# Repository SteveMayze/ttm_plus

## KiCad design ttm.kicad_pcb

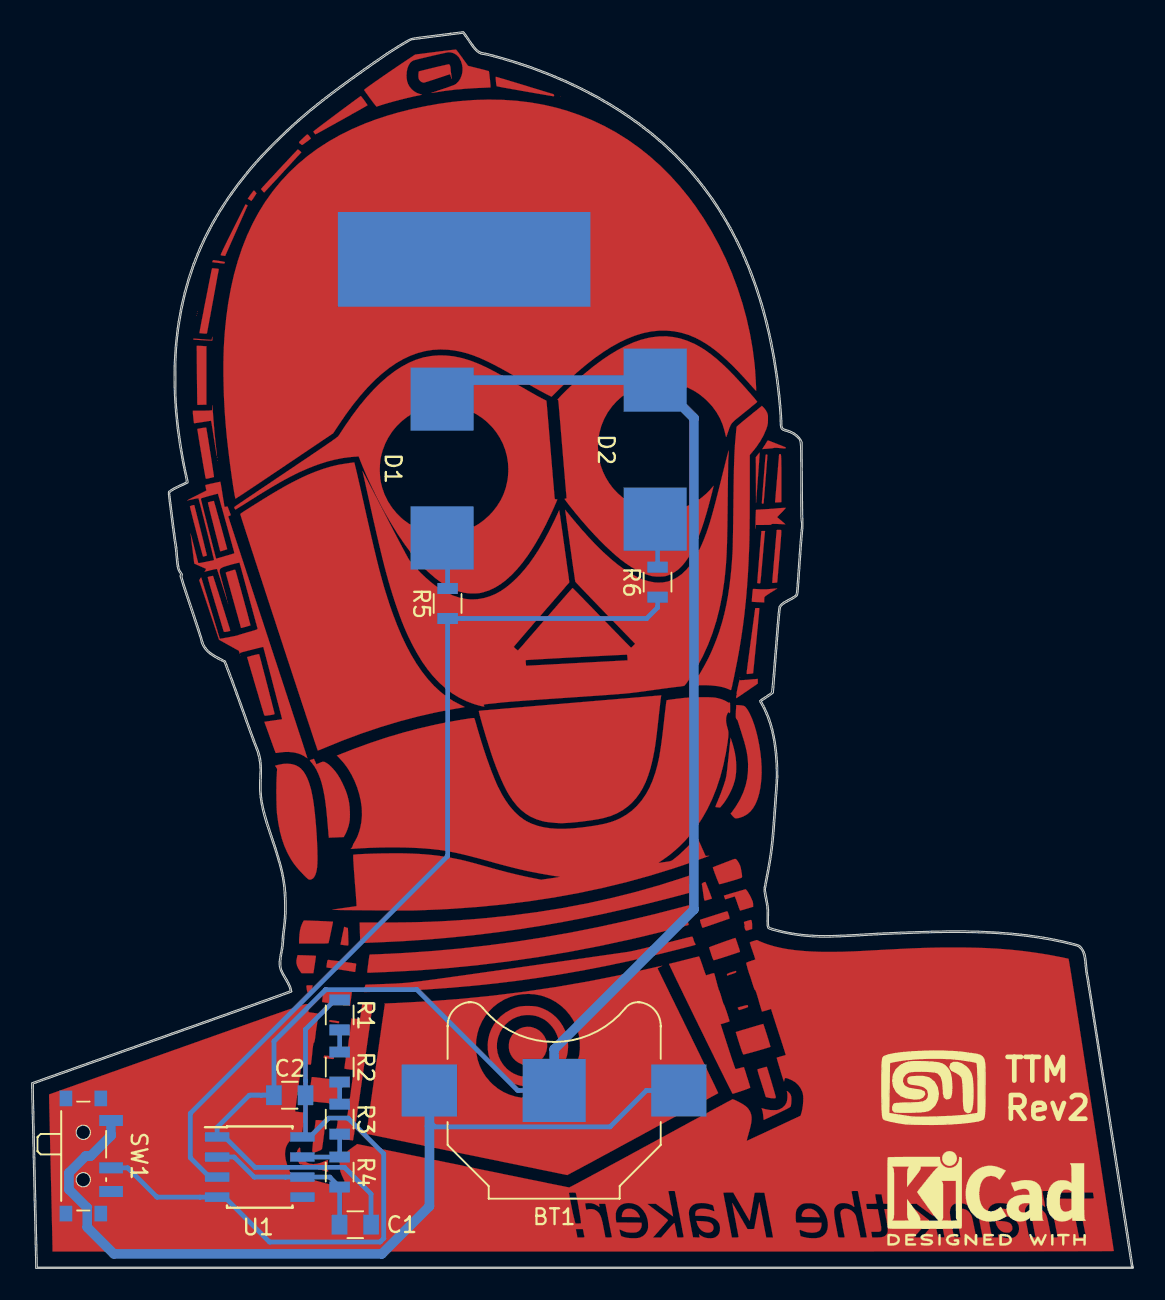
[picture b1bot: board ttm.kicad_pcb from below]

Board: 2 copper layers, 69.8 x 78.3 mm, 17 parts (15 on the bottom side), 10 nets.

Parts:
BT1: 3V; BatteryHolder_Keystone_3000_1x12mm
C1: 1μF; C_0805
C2: 0.1μF; C_0805
D1, D2: LED; LY_T77K_NH
Edge Cut: LOGO; c3po_EdgeCut
Front CU Text: LOGO; c3po_FCu_Text
KiCAD_Logo: KiCad-Logo2_6mm_SilkScreen
R1, R2, R3: 10MΩ; R_0805
R4: 750kΩ; R_0805
R5, R6: 400Ω; R_0805
SM_Logo: LOGO; MyBasic_rounded_50_1
SW1: SW_SPDT; SW_SPDT_PCM12
U1: NE555; SOIC-8_3.9x4.9mm_Pitch1.27mm

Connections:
+BATT: BT1.1, SW1.1
GND: BT1.2, C1.2, C2.2, D1.1, D2.1, U1.1
unnamed: C1.1, R4.2, U1.2, U1.6
unnamed: D1.2, R5.2
unnamed: D2.2, R6.2
unnamed: R1.2, R2.1
unnamed: R2.2, R3.1
unnamed: R3.2, R4.1, U1.7
unnamed: R5.1, R6.1, U1.3
VCC: C2.1, R1.1, SW1.2, U1.4, U1.8

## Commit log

2021-05-29 Recovered repository
